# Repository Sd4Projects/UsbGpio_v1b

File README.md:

# UsbGpio_v1b

Add gpio pins for (Mac, MiniPC, etc) via USB that do not have gpio pins to use.
If you only need a few gpio pins you may want to check out the Adafruit MCP2221 Breakout board Product ID: 4471.

UsbGpio board licensed under CERN OHL v.1.2 (Open Hardware Licence)

See CERN OHL v.1.2 for applicable conditions

http://ohwr.org/cernohl

USB Gpio Expansion board

Testing board design:

Top view of board:

Bottom view of board:

Schematic PDF file: UsbGpio_v1b.SCH.pdf

Board PDF file: UsbGpio_v1b.PCB.pdf

BOM PDF file: UsbGpio_v1b.BOM.pdf

Designed with KiCad Version 8.0.4

UsbGpio source files included.

UsbGpio board features:
1. Four 16bit AtoD lines using an ADS1115 chip via I2C interface
2. MCP23008 chip via I2C interface
3. Two GPIO pins driving 2N7002 Mosfets for output.
4. I2C lines to a JST_SH Connector
5. UART (Serial) lines to a JST_SH Connector
6. USB C connector, USB 2.0

All data lines use 4-pin Qwiic/JST_SH connectores.

Bare board can be ordered from: https://oshpark.com/shared_projects/wGhxM2sL

Python 3 test program run on a Mac from Terminal window: macTestMcp2221.py (There are python libraries for other types of systems.)

Parts used for testing:
1. 10K Precision Epoxy Thermistor - 3950 NTC From adafruit Product ID: 372
2. Monochrome 1.3" 128x64 OLED graphic display - STEMMA QT / Qwiic From adafruit Product ID: 938
3. Mini Panel Mount SPDT Toggle Switch From adafruit Product ID: 3221
4. STEMMA QT / Qwiic JST SH 4-Pin Cable - 50mm Long From adafruit Product ID: 4399

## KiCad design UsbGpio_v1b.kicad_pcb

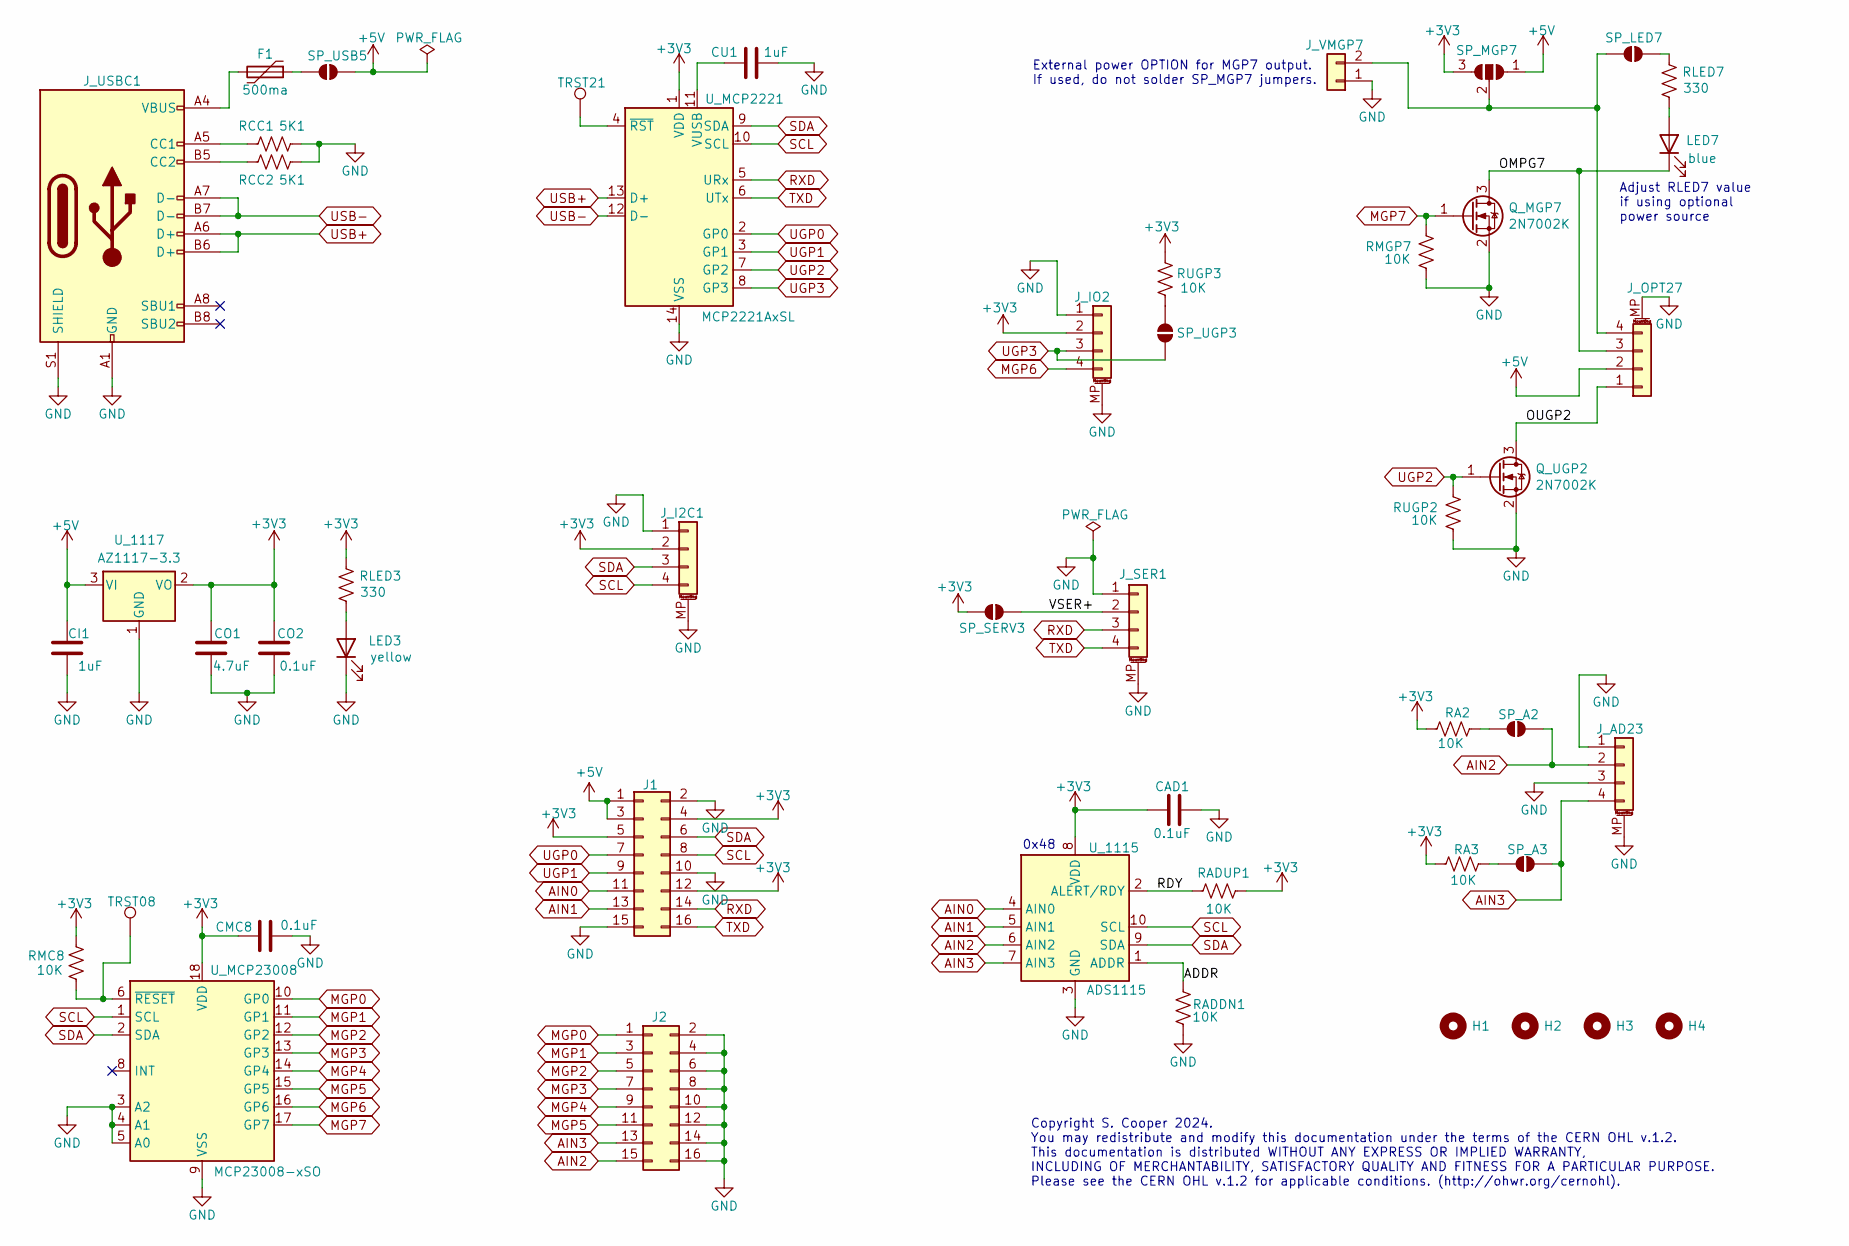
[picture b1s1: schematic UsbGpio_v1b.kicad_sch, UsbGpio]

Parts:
CAD1: 0.1uF; C_0805_2012Metric_Pad1.18x1.45mm_HandSolder; Manufacturer Part# C0805C104K3RAC7800; Digi-Key_PN 399-C0805C104K3RAC7800CT-ND
CI1: 1uF; C_0805_2012Metric_Pad1.18x1.45mm_HandSolder; Manufacturer Part# CL21B105KBFNNNE; Digi-Key_PN 1276-1029-1-ND
CMC8: 0.1uF; C_0805_2012Metric_Pad1.18x1.45mm_HandSolder; Manufacturer Part# C0805C104K3RAC7800; Digi-Key_PN 399-C0805C104K3RAC7800CT-ND
CO1: 4.7uF; C_0805_2012Metric_Pad1.18x1.45mm_HandSolder; Manufacturer Part# C0805C475K3PACTU; Digi-Key_PN 399-5505-1-ND
CO2: 0.1uF; C_0805_2012Metric_Pad1.18x1.45mm_HandSolder; Manufacturer Part# C0805C104K3RAC7800; Digi-Key_PN 399-C0805C104K3RAC7800CT-ND
CU1: 1uF; C_0805_2012Metric_Pad1.18x1.45mm_HandSolder; Manufacturer Part# CL21B105KBFNNNE; Digi-Key_PN 1276-1029-1-ND
F1: 500ma; Fuse_1812_4532Metric; Manufacturer Part# MF-MSMF050-2; Digi-Key_PN MF-PSMF050X-2CT-ND
H1, H2, H3, H4: MountingHole; MountingHole_3.2mm_M3
J1, J2: Conn_02x08_Odd_Even; PinHeader_2x08_P2.54mm_Vertical
J_AD23: Conn_01x04_MountingPin; JST_SH_SM04B-SRSS-TB_1x04-1MP_P1.00mm_Horizontal; Manufacturer Part# SM04B-SRSS-TB; Digi-Key_PN 455-SM04B-SRSS-TBCT-ND
J_I2C1: Conn_01x04_MountingPin; JST_SH_SM04B-SRSS-TB_1x04-1MP_P1.00mm_Horizontal; Manufacturer Part# SM04B-SRSS-TB; Digi-Key_PN 455-SM04B-SRSS-TBCT-ND
J_IO2: Conn_01x04_MountingPin; JST_SH_SM04B-SRSS-TB_1x04-1MP_P1.00mm_Horizontal; Manufacturer Part# SM04B-SRSS-TB; Digi-Key_PN 455-SM04B-SRSS-TBCT-ND
J_OPT27: Conn_01x04_MountingPin; JST_SH_SM04B-SRSS-TB_1x04-1MP_P1.00mm_Horizontal; Manufacturer Part# SM04B-SRSS-TB; Digi-Key_PN 455-SM04B-SRSS-TBCT-ND
J_SER1: Conn_01x04_MountingPin; JST_SH_SM04B-SRSS-TB_1x04-1MP_P1.00mm_Horizontal; Manufacturer Part# SM04B-SRSS-TB; Digi-Key_PN 455-SM04B-SRSS-TBCT-ND
J_USBC1: USB_C_Receptacle_USB2.0; USB_C_Receptacle_Palconn_UTC16-G_MOD; Manufacturer Part# USB4105-GF-A; Digi-Key_PN 2073-USB4105-GF-ACT-ND
J_VMGP7: Conn_01x02; PinHeader_1x02_P2.54mm_Vertical
LED3: yellow; LED_0805_2012Metric_Pad1.15x1.40mm_HandSolder; Manufacturer Part# LTST-C170KSKT; Digi-Key_PN 160-1416-1-ND
LED7: blue; LED_0805_2012Metric_Pad1.15x1.40mm_HandSolder; Manufacturer Part# C171TBKT; Digi-Key_PN 160-1645-1-ND
Q_MGP7: 2N7002K; SOT-23_Handsoldering; Manufacturer Part# 2N7002K; Digi-Key_PN 2N7002KCT-ND
Q_UGP2: 2N7002K; SOT-23_Handsoldering; Manufacturer Part# 2N7002K; Digi-Key_PN 2N7002KCT-ND
RA2, RA3: 10K; R_0805_2012Metric_Pad1.20x1.40mm_HandSolder; Manufacturer Part# AC0805FR-0710KL; Digi-Key_PN 311-10KLGCT-ND
RADDN1: 10K; R_0805_2012Metric_Pad1.20x1.40mm_HandSolder; Manufacturer Part# AC0805FR-0710KL; Digi-Key_PN 311-10KLGCT-ND
RADUP1: 10K; R_0805_2012Metric_Pad1.20x1.40mm_HandSolder; Manufacturer Part# AC0805FR-0710KL; Digi-Key_PN 311-10KLGCT-ND
RCC1, RCC2: 5K1; R_0805_2012Metric; Manufacturer Part# RC0805FR-075K1L; Digi-Key_PN 311-5.10KCRCT-ND
RLED3, RLED7: 330; R_0805_2012Metric; Manufacturer Part# RC0805FR-07330RL; Digi-Key_PN 311-330CRCT-ND
RMC8: 10K; R_0805_2012Metric_Pad1.20x1.40mm_HandSolder; Manufacturer Part# AC0805FR-0710KL; Digi-Key_PN 311-10KLGCT-ND
RMGP7: 10K; R_0805_2012Metric_Pad1.20x1.40mm_HandSolder; Manufacturer Part# AC0805FR-0710KL; Digi-Key_PN 311-10KLGCT-ND
RUGP2, RUGP3: 10K; R_0805_2012Metric_Pad1.20x1.40mm_HandSolder; Manufacturer Part# AC0805FR-0710KL; Digi-Key_PN 311-10KLGCT-ND
SP_A2, SP_A3: SolderJumper_2_Open; SolderJumper-2_P1.3mm_Open_Pad1.0x1.5mm
SP_LED7: SolderJumper_2_Open; SolderJumper-2_P1.3mm_Open_Pad1.0x1.5mm
SP_MGP7: SolderJumper_3_Open; SolderJumper-3_P1.3mm_Open_Pad1.0x1.5mm
SP_SERV3: SolderJumper_2_Open; SolderJumper-2_P1.3mm_Open_Pad1.0x1.5mm
SP_UGP3: SolderJumper_2_Open; SolderJumper-2_P1.3mm_Open_Pad1.0x1.5mm
SP_USB5: SolderJumper_2_Open; SolderJumper-2_P1.3mm_Open_Pad1.0x1.5mm
TRST08, TRST21: TestPoint; TestPoint_Pad_D2.0mm
U_1115: ADS1115; MSOP-10_3x3mm_P0.5mm_MOD; Manufacturer Part# ADS1115IDGST; Digi-Key_PN 296-24934-1-ND
U_1117: AZ1117-3.3; SOT-223-3_TabPin2; Manufacturer Part# AZ1117CH-3.3TRG1; Digi-Key_PN AZ1117CH-3.3TRG1DICT-ND
U_MCP2221: MCP2221AxSL; SOIC-14_3.9x8.7mm_P1.27mm; Manufacturer Part# MCP2221A-I/SL; Digi-Key_PN MCP2221A-I/SL-ND
U_MCP23008: MCP23008-xSO; SOIC-18W_7.5x11.6mm_P1.27mm; Manufacturer Part# MCP23008T-E/SO; Digi-Key_PN MCP23008T-E/SOCT-ND

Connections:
+3V3: CAD1.2, CMC8.2, CO1.1, CO2.1, J1.4, J1.5, J1.12, J_I2C1.2, J_IO2.2, RA2.2, RA3.2, RADUP1.2, RLED3.2, RMC8.2, RUGP3.1, SP_MGP7.3 (B), SP_SERV3.1 (A), U_1115.8 (VDD), U_1117.2 (VO), U_MCP2221.1 (VDD), U_MCP23008.18 (VDD)
+5V: CI1.1, J1.1, J1.3, J_OPT27.2, SP_MGP7.1 (A), SP_USB5.2 (B), U_1117.3 (VI)
/ADDR: RADDN1.2, U_1115.1 (ADDR)
/OMPG7: J_OPT27.3, LED7.1 (K), Q_MGP7.3 (D)
/OUGP2: J_OPT27.1, Q_UGP2.3 (D)
/RDY: RADUP1.1, U_1115.2 (ALERT/RDY)
/VSER+: J_SER1.2, SP_SERV3.2 (B)
AIN0: J1.11, U_1115.4 (AIN0)
AIN1: J1.13, U_1115.5 (AIN1)
AIN2: J2.15, J_AD23.2, SP_A2.1 (A), U_1115.6 (AIN2)
AIN3: J2.13, J_AD23.4, SP_A3.1 (A), U_1115.7 (AIN3)
GND: CAD1.1, CI1.2, CMC8.1, CO1.2, CO2.2, CU1.2, J1.2, J1.10, J1.15, J2.2, J2.4, J2.6, J2.8, J2.10, J2.12, J2.14, J2.16, J_AD23.1, J_AD23.3, J_AD23.MP (MountPin), J_I2C1.1, J_I2C1.MP (MountPin), J_IO2.1, J_IO2.MP (MountPin), J_OPT27.MP (MountPin), J_SER1.1, J_SER1.MP (MountPin), J_USBC1.A1 (GND), J_USBC1.A12 (GND), J_USBC1.B1 (GND), J_USBC1.B12 (GND), J_USBC1.S1 (SHIELD), J_VMGP7.1, LED3.1 (K), Q_MGP7.2 (S), Q_UGP2.2 (S), RADDN1.1, RCC1.2, RCC2.2, RMGP7.2, RUGP2.2, U_1115.3 (GND), U_1117.1 (GND), U_MCP2221.14 (VSS), U_MCP23008.3 (A2), U_MCP23008.4 (A1), U_MCP23008.5 (A0), U_MCP23008.9 (VSS)
MGP0: J2.1, U_MCP23008.10 (GP0)
MGP1: J2.3, U_MCP23008.11 (GP1)
MGP2: J2.5, U_MCP23008.12 (GP2)
MGP3: J2.7, U_MCP23008.13 (GP3)
MGP4: J2.9, U_MCP23008.14 (GP4)
MGP5: J2.11, U_MCP23008.15 (GP5)
MGP6: J_IO2.4, U_MCP23008.16 (GP6)
MGP7: Q_MGP7.1 (G), RMGP7.1, U_MCP23008.17 (GP7)
unnamed: F1.2, J_USBC1.A4 (VBUS), J_USBC1.A9 (VBUS), J_USBC1.B4 (VBUS), J_USBC1.B9 (VBUS)
unnamed: J_OPT27.4, J_VMGP7.2, SP_LED7.1 (A), SP_MGP7.2 (C)
unnamed: J_USBC1.A5 (CC1), RCC1.1
unnamed: J_USBC1.B5 (CC2), RCC2.1
unnamed: LED3.2 (A), RLED3.1
unnamed: LED7.2 (A), RLED7.1
unnamed: RA2.1, SP_A2.2 (B)
unnamed: RA3.1, SP_A3.2 (B)
unnamed: RLED7.2, SP_LED7.2 (B)
unnamed: RUGP3.2, SP_UGP3.1 (A)
unnamed: F1.1, SP_USB5.1 (A)
unnamed: CU1.1, U_MCP2221.11 (VUSB)
unnamed: TRST21.1, U_MCP2221.4 (~RST)
unnamed: RMC8.1, TRST08.1, U_MCP23008.6 (~RESET)
RXD: J1.14, J_SER1.3, U_MCP2221.5 (URx)
SCL: J1.8, J_I2C1.4, U_1115.10 (SCL), U_MCP2221.10 (SCL), U_MCP23008.1 (SCL)
SDA: J1.6, J_I2C1.3, U_1115.9 (SDA), U_MCP2221.9 (SDA), U_MCP23008.2 (SDA)
TXD: J1.16, J_SER1.4, U_MCP2221.6 (UTx)
UGP0: J1.7, U_MCP2221.2 (GP0)
UGP1: J1.9, U_MCP2221.3 (GP1)
UGP2: Q_UGP2.1 (G), RUGP2.1, U_MCP2221.7 (GP2)
UGP3: J_IO2.3, SP_UGP3.2 (B), U_MCP2221.8 (GP3)
USB+: J_USBC1.A6 (D+), J_USBC1.B6 (D+), U_MCP2221.13 (D+)
USB-: J_USBC1.A7 (D-), J_USBC1.B7 (D-), U_MCP2221.12 (D-)

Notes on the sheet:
External power OPTION for MGP7 output. If used, do not solder SP_MGP7 jumpers.
0x48
Adjust RLED7 value if using optional power source
Copyright S. Cooper 2024. You may redistribute and modify this documentation under the terms of the CERN OHL v.1.2. This documentation is distributed WITHOUT ANY EXPRESS OR IMPLIED WARRANTY, INCLUDING OF MERCHANTABILITY, SATISFACTORY QUALITY AND FITNESS FOR A PARTICULAR PURPOSE. Please see the CERN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

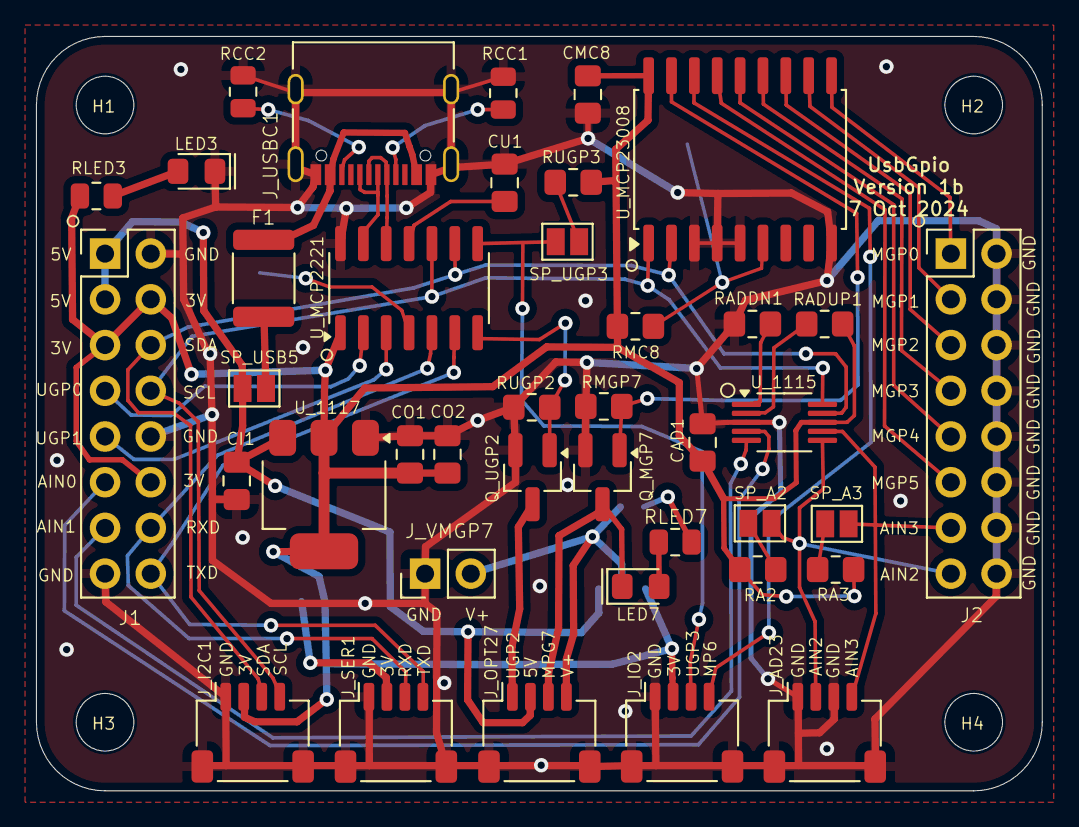
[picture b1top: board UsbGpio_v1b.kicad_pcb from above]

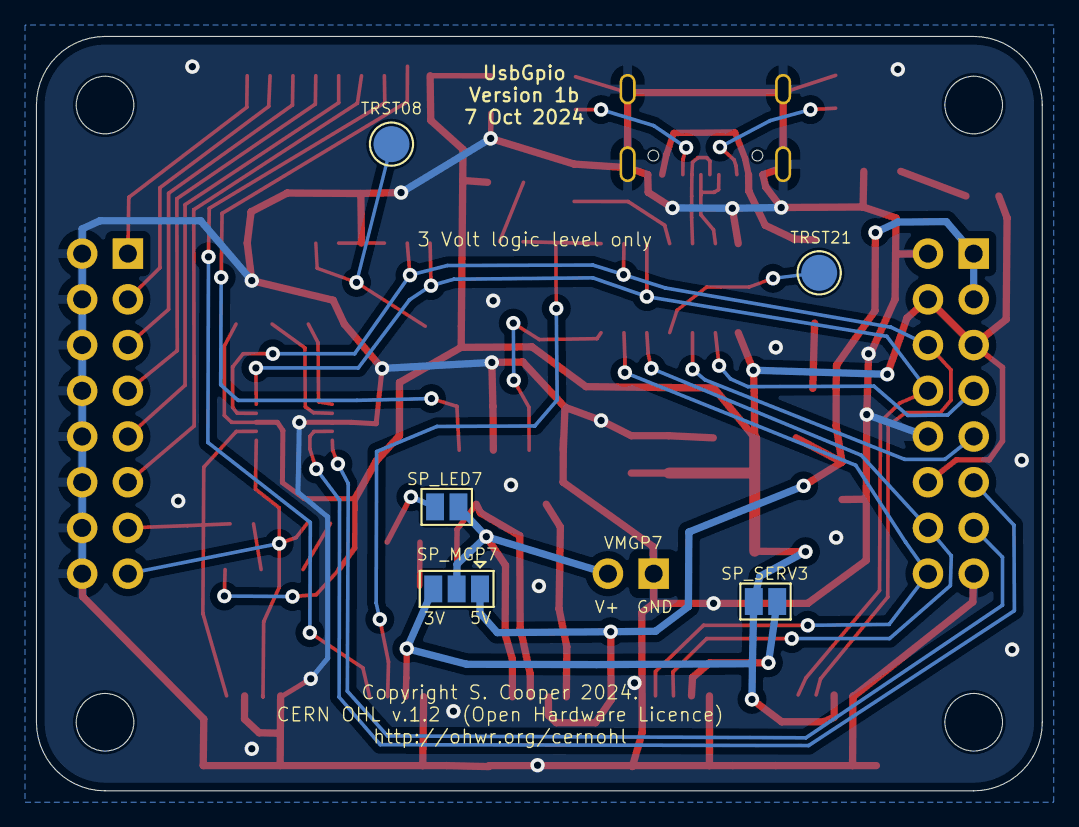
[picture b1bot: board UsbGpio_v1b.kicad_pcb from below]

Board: 2 copper layers, 55.9 x 41.9 mm, 49 parts (5 on the bottom side), 44 nets.
